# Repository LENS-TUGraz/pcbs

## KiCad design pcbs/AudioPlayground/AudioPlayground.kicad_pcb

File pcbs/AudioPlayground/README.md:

# LE Audio Playground

**An open hardware platform for Bluetooth LE Audio research, prototyping, and teaching.**

The **LE Audio Playground** is a compact development platform designed to make experimenting with **Bluetooth LE Audio** simple and accessible. Built around the **Nordic nRF5340**, it combines a powerful Bluetooth SoC with stereo audio, integrated debugging, USB connectivity, battery operation, and flexible expansion in a single open hardware platform.

Designed at **Graz University of Technology**, the board provides a practical foundation for LE Audio research, prototyping, and education while remaining fully open and easy to extend.

## Highlights

- **Nordic nRF5340** dual-core Bluetooth SoC
- **MAX9867 stereo audio codec**
- Analog audio input and output
- **USB Audio** connectivity
- Onboard digital **PDM microphones**
- Integrated **SEGGER J-Link** debugging and programming
- Single **USB-C** connection
- USB and **LiPo/Li-ion battery operation**
- Onboard antenna
- Expansion headers for custom hardware and audio interfaces
- Fully **open KiCad hardware design**

## Open Hardware

The complete schematic and PCB design are available in this repository and can be modified directly in **KiCad**.

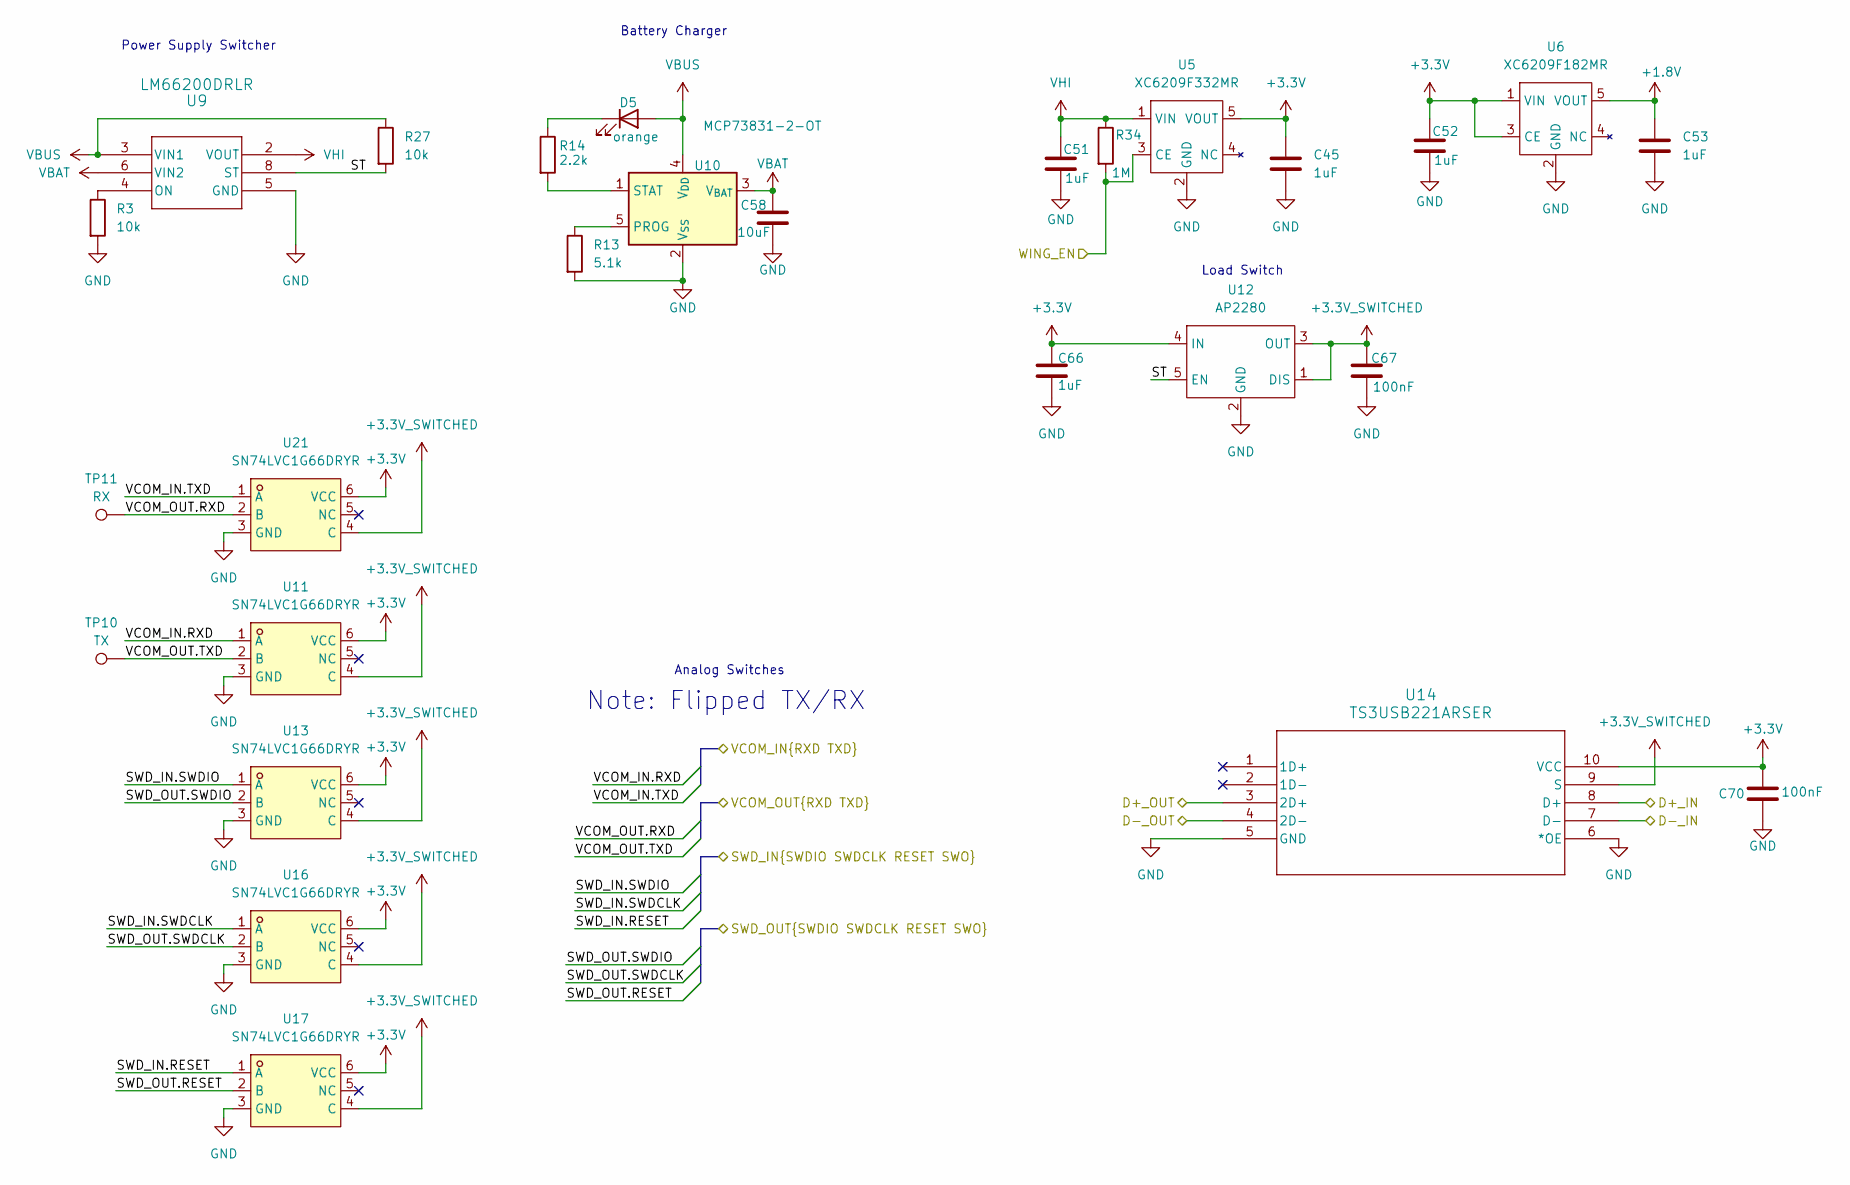
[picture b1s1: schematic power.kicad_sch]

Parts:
C45, C51, C52, C53, C66: 1uF; C_0402_1005Metric; MOUSER 81-GRM155Z71A105KE1D
C58: 10uF; C_0402_1005Metric; MOUSER 187-CL05A106MQ5NRNC
C67, C70: 100nF; C_0402_1005Metric; MOUSER 80-C0402C104M4R
D5: orange; LED_0402_1005Metric; MOUSER 78-VLMO1500-GS08
R3, R27: 10k; R_0402_1005Metric; MOUSER 660-RN73R1ETP1002F50
R13: 5.1k; R_0402_1005Metric; MOUSER 594-MCS04020C5102FE0
R14: 2.2k; R_0402_1005Metric; MOUSER 603-AC0402FR-7D2K2L
R34: 1M; R_0402_1005Metric; MOUSER 279-CRGCQ0402J1M0
TP10: TX; TestPoint_Pad_D1.0mm
TP11: RX; TestPoint_Pad_D1.0mm
U5: XC6209F332MR; SOT-23-5_HandSoldering; MOUSER 865-XC6209F332MR-G
U6: XC6209F182MR; SOT-23-5_HandSoldering; MOUSER 865-XC6209F332MR-G
U9: LM66200DRLR; LM662; MOUSER 595-LM66200DRLR
U10: MCP73831-2-OT; SOT-23-5; MOUSER 579-MCP73832T2DFI/OT
U11, U13, U16, U17, U21: SN74LVC1G66DRYR; LCSC Part C507245
U12: AP2280; SOT-23-5; MOUSER 621-AP2280-1WG-7
U14: TS3USB221ARSER; TS3USB221A; LCSC C128396

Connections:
+1.8V: C53.1, U6.5 (VOUT); also elsewhere on the board
+3.3V: C45.1, C52.1, C66.1, C70.1, U5.5 (VOUT), U6.1 (VIN), U6.3 (CE), U11.6 (VCC), U12.4 (IN), U13.6 (VCC), U14.10 (VCC), U16.6 (VCC), U17.6 (VCC), U21.6 (VCC); also elsewhere on the board
+3.3V_SWITCHED: C67.1, U11.4 (C), U12.1 (DIS), U12.3 (OUT), U13.4 (C), U14.9 (S), U16.4 (C), U17.4 (C), U21.4 (C); also elsewhere on the board
/IO/WING_EN: R34.2, U5.3 (CE); also elsewhere on the board
/Interface MCU/SWD.RESET: U17.1 (A); also elsewhere on the board
/Interface MCU/SWD.SWDCLK: U16.1 (A); also elsewhere on the board
/Interface MCU/SWD.SWDIO: U13.1 (A); also elsewhere on the board
/Interface MCU/VCOM.RXD: U11.1 (A); also elsewhere on the board
/Interface MCU/VCOM.TXD: U21.1 (A); also elsewhere on the board
/MCU/D+: U14.3 (2D+); also elsewhere on the board
/MCU/D-: U14.4 (2D-); also elsewhere on the board
/MCU/SWD.RESET: U17.2 (B); also elsewhere on the board
/MCU/SWD.SWDCLK: U16.2 (B); also elsewhere on the board
/MCU/SWD.SWDIO: U13.2 (B); also elsewhere on the board
/MCU/VCOM.RXD: TP11.1, U21.2 (B); also elsewhere on the board
/MCU/VCOM.TXD: TP10.1, U11.2 (B); also elsewhere on the board
/Power/D+_IN: U14.8 (D+); also elsewhere on the board
/Power/D-_IN: U14.7 (D-); also elsewhere on the board
/Power/ST: R27.2, U9.8 (ST), U12.5 (EN)
GND: C45.2, C51.2, C52.2, C53.2, C58.2, C66.2, C67.2, C70.2, R3.2, R13.2, U5.2 (GND), U6.2 (GND), U9.1 (GND), U9.5 (GND), U10.2 (V_{SS}), U11.3 (GND), U12.2 (GND), U13.3 (GND), U14.5 (GND), U14.6 (*OE), U16.3 (GND), U17.3 (GND), U21.3 (GND); also elsewhere on the board
unnamed: D5.1 (K), R14.1
unnamed: R3.1, U9.4 (ON)
unnamed: R13.1, U10.5 (PROG)
unnamed: R14.2, U10.1 (STAT)
VBAT: C58.1, U9.6 (VIN2), U10.3 (V_{BAT}); also elsewhere on the board
VBUS: D5.2 (A), R27.1, U9.3 (VIN1), U10.4 (V_{DD}); also elsewhere on the board
VHI: C51.1, R34.1, U5.1 (VIN), U9.2 (VOUT), U9.7 (VOUT); also elsewhere on the board

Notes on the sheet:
Note: Flipped TX/RX
Analog Switches
Battery Charger
Power Supply Switcher
Load Switch

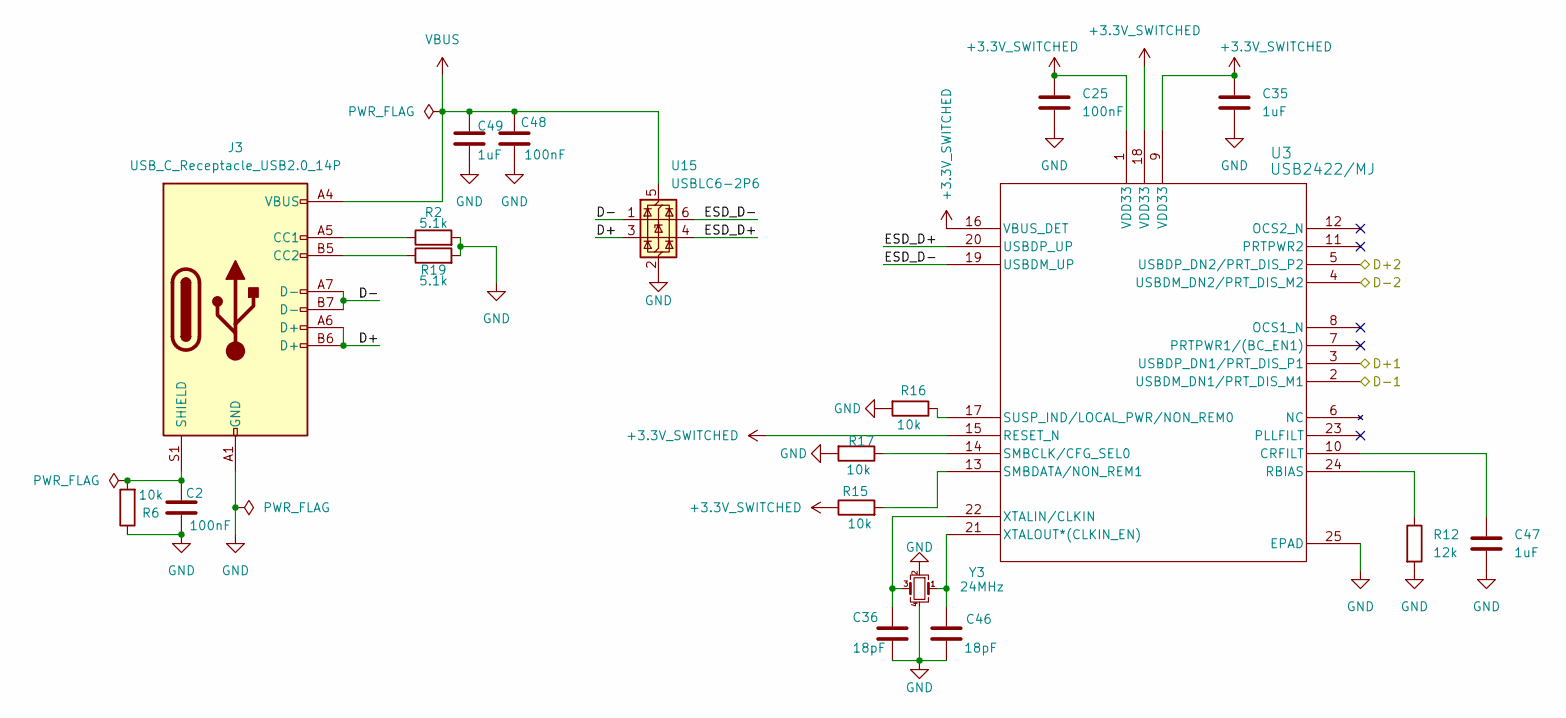
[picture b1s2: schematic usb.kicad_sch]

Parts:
C2, C25, C48: 100nF; C_0402_1005Metric; MOUSER 80-C0402C104M4R
C35, C47, C49: 1uF; C_0402_1005Metric; MOUSER 81-GRM155Z71A105KE1D
C36, C46: 18pF; C_0402_1005Metric; MOUSER 581-04025A180F4T2A
J3: USB_C_Receptacle_USB2.0_14P; USB_C_Receptacle_GCT_USB4105-xx-A_16P_TopMnt_Horizontal; MOUSER 640-USB4105-GF-A
R2, R19: 5.1k; R_0402_1005Metric; MOUSER 667-ERJ-2RHD5101X
R6: 10k; R_0402_1005Metric; MOUSER 660-RN73R1ETP1002F50
R12: 12k; R_0402_1005Metric; MOUSER 652-CR0402FX-1202GLF
R15, R16, R17: 10k; R_0402_1005Metric; MOUSER 594-MCS04020C5102FE0
U3: USB2422/MJ; USB2422; MOUSER 579-USB2422T/MJ
U15: USBLC6-2P6; SOT-666; LCSC C15999
Y3: 24MHz; Crystal_SMD_3225-4Pin_3.2x2.5mm; MOUSER 732-322524F20GAC0

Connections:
+3.3V_SWITCHED: C25.1, C35.1, R15.1, U3.1 (VDD33), U3.9 (VDD33), U3.15 (RESET_N), U3.16 (VBUS_DET), U3.18 (VDD33); also elsewhere on the board
/Interface MCU/D+: U3.5 (USBDP_DN2/PRT_DIS_P2); also elsewhere on the board
/Interface MCU/D-: U3.4 (USBDM_DN2/PRT_DIS_M2); also elsewhere on the board
/Power/D+_IN: U3.3 (USBDP_DN1/PRT_DIS_P1); also elsewhere on the board
/Power/D-_IN: U3.2 (USBDM_DN1/PRT_DIS_M1); also elsewhere on the board
/USB Port/D+: J3.A6 (D+), J3.B6 (D+), U15.3 (I/O2)
/USB Port/D-: J3.A7 (D-), J3.B7 (D-), U15.1 (I/O1)
/USB Port/ESD_D+: U3.20 (USBDP_UP), U15.4 (I/O2)
/USB Port/ESD_D-: U3.19 (USBDM_UP), U15.6 (I/O1)
GND: C2.2, C25.2, C35.2, C36.2, C46.2, C47.2, C48.2, C49.2, J3.A1 (GND), J3.A12 (GND), J3.B1 (GND), J3.B12 (GND), R2.2, R6.1, R12.2, R16.2, R17.2, R19.2, U3.25 (EPAD), U15.2 (GND), Y3.2, Y3.4; also elsewhere on the board
unnamed: J3.A5 (CC1), R2.1
unnamed: J3.B5 (CC2), R19.1
unnamed: C2.1, J3.S1 (SHIELD), R6.2
unnamed: C47.1, U3.10 (CRFILT)
unnamed: R12.1, U3.24 (RBIAS)
unnamed: R17.1, U3.14 (SMBCLK/CFG_SEL0)
unnamed: R15.2, U3.13 (SMBDATA/NON_REM1)
unnamed: R16.1, U3.17 (SUSP_IND/LOCAL_PWR/NON_REM0)
unnamed: C36.1, U3.22 (XTALIN/CLKIN), Y3.3
unnamed: C46.1, U3.21 (XTALOUT*(CLKIN_EN)), Y3.1
VBUS: C48.1, C49.1, J3.A4 (VBUS), J3.A9 (VBUS), J3.B4 (VBUS), J3.B9 (VBUS), U15.5 (VBUS); also elsewhere on the board

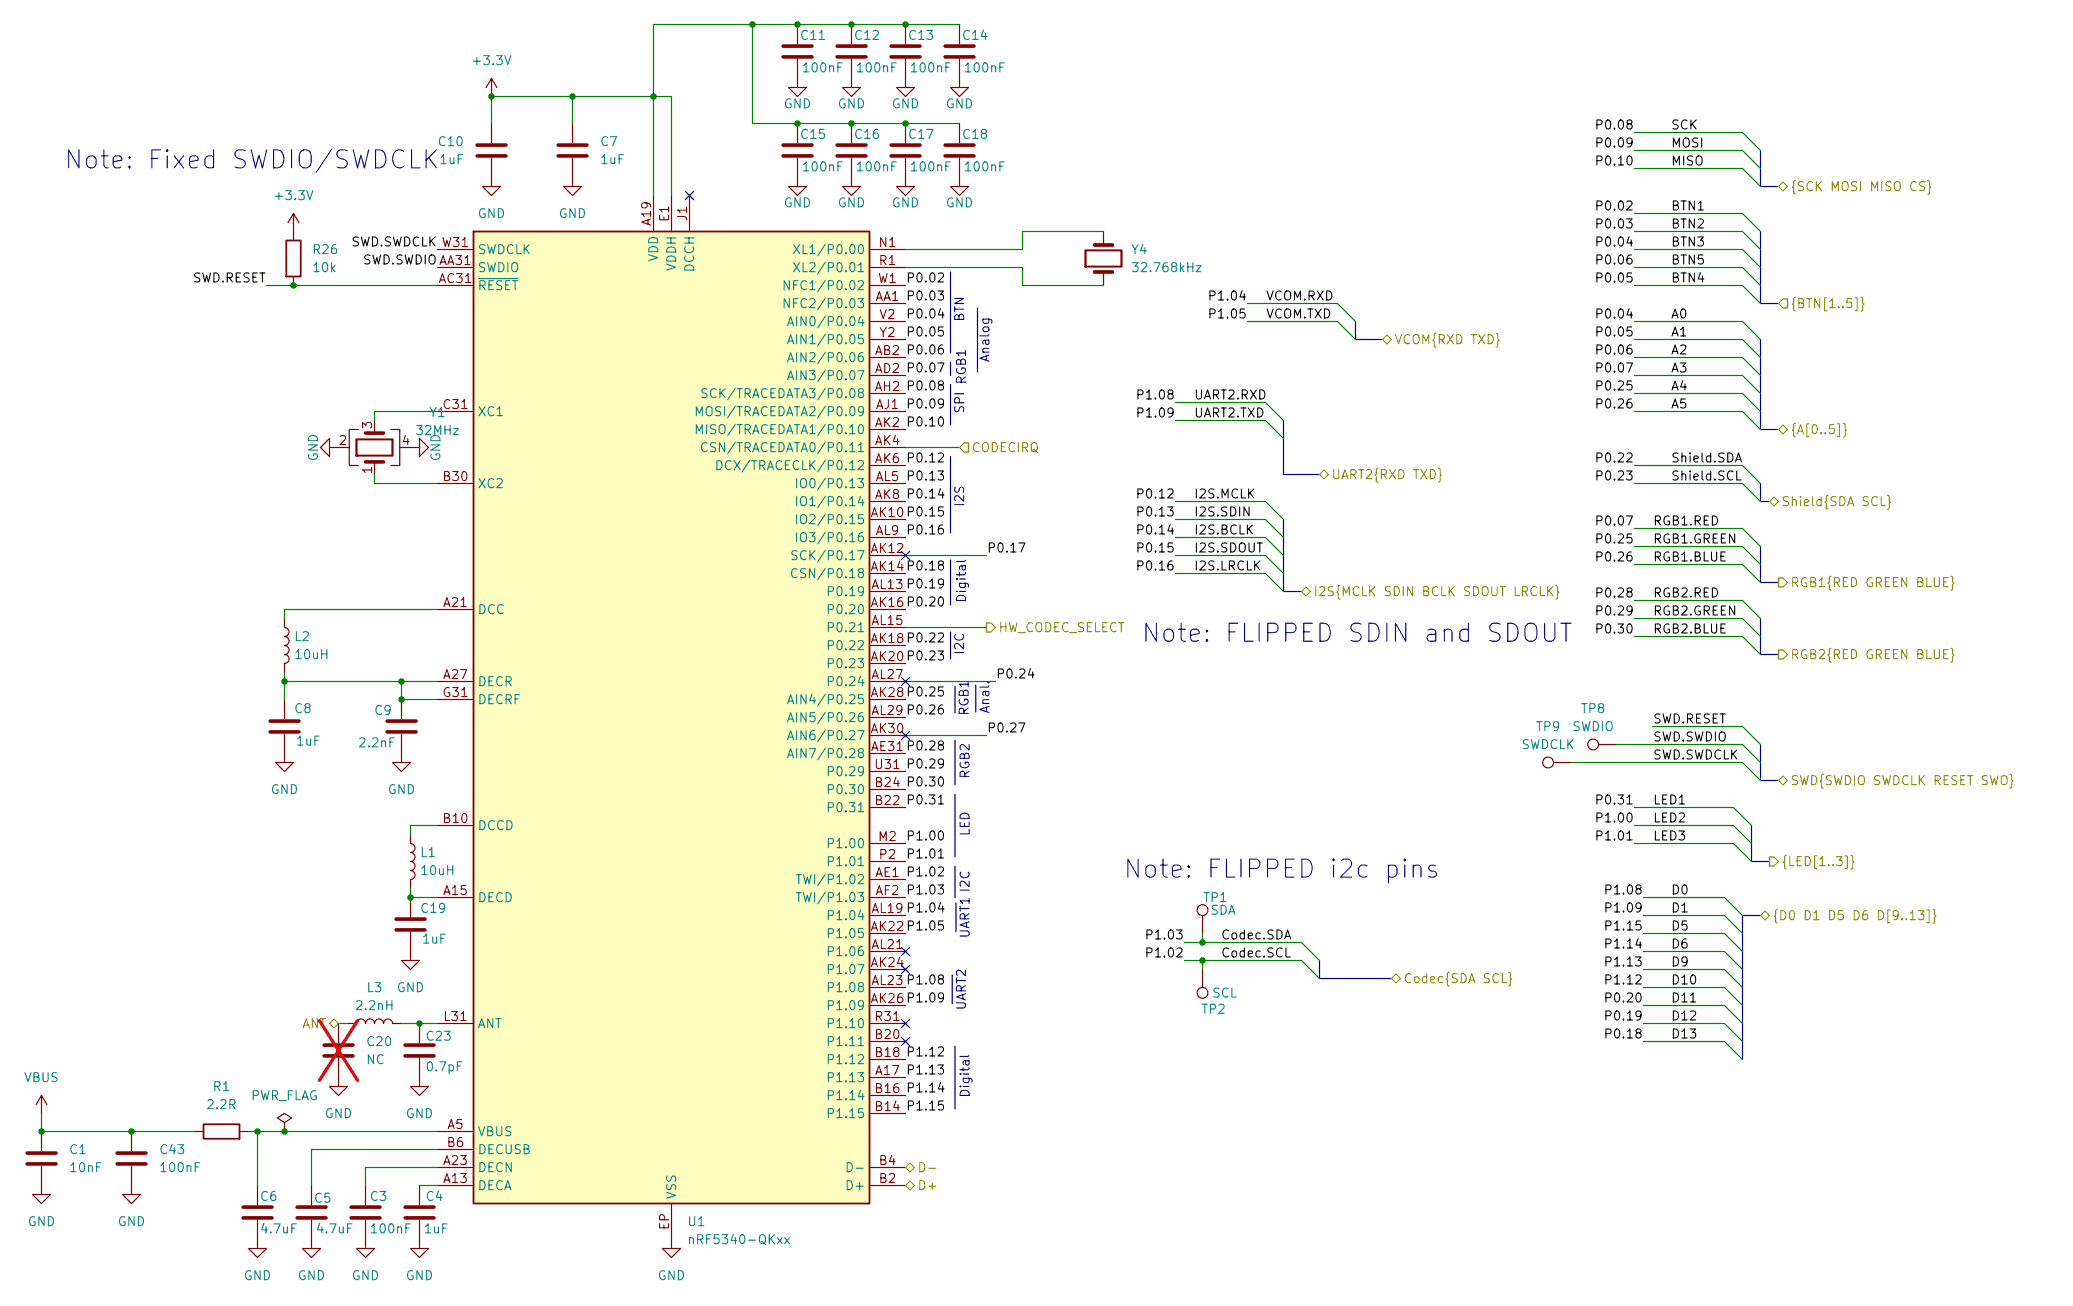
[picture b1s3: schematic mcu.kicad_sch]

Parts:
C1: 10nF; C_0402_1005Metric; MOUSER 80-C0402C103K8RLR
C3, C11, C12, C13, C14, C15, C16, C17, C18, C43: 100nF; C_0402_1005Metric; MOUSER 80-C0402C104M4R
C4, C7, C8, C10, C19: 1uF; C_0402_1005Metric; MOUSER 81-GRM155Z71A105KE1D
C5, C6: 4.7uF; C_0402_1005Metric; MOUSER 603-CC0402KR5R6BB475
C9: 2.2nF; C_0402_1005Metric; MOUSER 581-04023C222KAT2A
C20: NC; C_0402_1005Metric; not fitted
C23: 0.7pF; C_0402_1005Metric; MOUSER 581-04025U0R7BAT2A
L1, L2: 10uH; L_0402_1005Metric; MOUSER 81-LQW15DN100M00D
L3: 2.2nH; L_0402_1005Metric; MOUSER 815-AISCQ0402HQ2N2CT
R1: 2.2R; R_0402_1005Metric; MOUSER 667-ERJ-U02F2R20X
R26: 10k; R_0402_1005Metric; MOUSER 660-RN73R1ETP1002F50
TP1: SDA; TestPoint_Pad_D1.0mm
TP2: SCL; TestPoint_Pad_D1.0mm
TP8: SWDIO; TestPoint_Pad_D1.0mm
TP9: SWDCLK; TestPoint_Pad_D1.0mm
U1: nRF5340-QKxx; Nordic_AQFN-94-1EP_7x7mm_P0.4mm; MOUSER 949-NRF5340-QKAA-R7
Y1: 32MHz; Crystal_SMD_3225-4Pin_3.2x2.5mm; MOUSER 581-CX3225GB32DHEQCC
Y4: 32.768kHz; Crystal_SMD_3215-2Pin_3.2x1.5mm; MOUSER 732-FC135-32.76KAAC3

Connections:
+3.3V: C7.1, C10.2, C11.1, C12.1, C13.1, C14.1, C15.1, C16.1, C17.1, C18.1, R26.1, U1.A19 (VDD), U1.AC1 (VDD), U1.AG1 (VDD), U1.AJ31 (VDD), U1.AL3 (VDD), U1.AL7 (VDD), U1.AL11 (VDD), U1.AL17 (VDD), U1.AL25 (VDD), U1.B8 (VDD), U1.B28 (VDD), U1.C1 (VDD), U1.E1 (VDDH), U1.E31 (VDD), U1.L1 (VDD), U1.N31 (VDD), U1.U1 (VDD); also elsewhere on the board
/Audio Codec/Codec.SCL: TP2.1, U1.AE1 (TWI/P1.02); also elsewhere on the board
/Audio Codec/Codec.SDA: TP1.1, U1.AF2 (TWI/P1.03); also elsewhere on the board
/Audio Codec/I2S.BCLK: U1.AK8 (IO1/P0.14); also elsewhere on the board
/Audio Codec/I2S.LRCLK: U1.AL9 (IO3/P0.16); also elsewhere on the board
/Audio Codec/I2S.MCLK: U1.AK6 (DCX/TRACECLK/P0.12); also elsewhere on the board
/Audio Codec/I2S.SDIN: U1.AL5 (IO0/P0.13); also elsewhere on the board
/Audio Codec/I2S.SDOUT: U1.AK10 (IO2/P0.15); also elsewhere on the board
/Audio Codec/IRQ: U1.AK4 (CSN/TRACEDATA0/P0.11); also elsewhere on the board
/IO/A0: U1.V2 (AIN0/P0.04); also elsewhere on the board
/IO/A1: U1.Y2 (AIN1/P0.05); also elsewhere on the board
/IO/A2: U1.AB2 (AIN2/P0.06); also elsewhere on the board
/IO/A3: U1.AD2 (AIN3/P0.07); also elsewhere on the board
/IO/A4: U1.AK28 (AIN4/P0.25); also elsewhere on the board
/IO/A5: U1.AL29 (AIN5/P0.26); also elsewhere on the board
/IO/ANT: C20.1, L3.1; also elsewhere on the board
/IO/BTN1: U1.W1 (NFC1/P0.02); also elsewhere on the board
/IO/BTN2: U1.AA1 (NFC2/P0.03); also elsewhere on the board
/IO/D0: U1.AL23 (P1.08); also elsewhere on the board
/IO/D1: U1.AK26 (P1.09); also elsewhere on the board
/IO/D5: U1.B14 (P1.15); also elsewhere on the board
/IO/D6: U1.B16 (P1.14); also elsewhere on the board
/IO/D9: U1.A17 (P1.13); also elsewhere on the board
/IO/D10: U1.B18 (P1.12); also elsewhere on the board
/IO/D11: U1.AK16 (P0.20); also elsewhere on the board
/IO/D12: U1.AL13 (P0.19); also elsewhere on the board
/IO/D13: U1.AK14 (CSN/P0.18); also elsewhere on the board
/IO/LED1: U1.B22 (P0.31); also elsewhere on the board
/IO/LED2: U1.M2 (P1.00); also elsewhere on the board
/IO/LED3: U1.P2 (P1.01); also elsewhere on the board
/IO/MISO: U1.AK2 (MISO/TRACEDATA1/P0.10); also elsewhere on the board
/IO/MOSI: U1.AJ1 (MOSI/TRACEDATA2/P0.09); also elsewhere on the board
/IO/SCK: U1.AH2 (SCK/TRACEDATA3/P0.08); also elsewhere on the board
/IO/SCL: U1.AK20 (P0.23); also elsewhere on the board
/IO/SDA: U1.AK18 (P0.22); also elsewhere on the board
/MCU/D+: U1.B2 (D+); also elsewhere on the board
/MCU/D-: U1.B4 (D-); also elsewhere on the board
/MCU/HW_CODEC_SELECT: U1.AL15 (P0.21)
/MCU/P0.17: U1.AK12 (SCK/P0.17)
/MCU/P0.24: U1.AL27 (P0.24)
/MCU/P0.27: U1.AK30 (AIN6/P0.27)
/MCU/RGB2.BLUE: U1.B24 (P0.30)
/MCU/RGB2.GREEN: U1.U31 (P0.29)
/MCU/RGB2.RED: U1.AE31 (AIN7/P0.28)
/MCU/SWD.RESET: R26.2, U1.AC31 (~RESET); also elsewhere on the board
/MCU/SWD.SWDCLK: TP9.1, U1.W31 (SWDCLK); also elsewhere on the board
/MCU/SWD.SWDIO: TP8.1, U1.AA31 (SWDIO); also elsewhere on the board
/MCU/VCOM.RXD: U1.AL19 (P1.04); also elsewhere on the board
/MCU/VCOM.TXD: U1.AK22 (P1.05); also elsewhere on the board
GND: C1.2, C3.2, C4.2, C5.2, C6.2, C7.2, C8.2, C9.2, C10.1, C11.2, C12.2, C13.2, C14.2, C15.2, C16.2, C17.2, C18.2, C19.2, C20.2, C23.2, C43.2, U1.EP (VSS), Y1.2, Y1.4; also elsewhere on the board
unnamed: C23.1, L3.2, U1.L31 (ANT)
unnamed: L2.1, U1.A21 (DCC)
unnamed: L1.1, U1.B10 (DCCD)
unnamed: C4.1, U1.A13 (DECA)
unnamed: C19.1, L1.2, U1.A15 (DECD)
unnamed: C3.1, U1.A23 (DECN)
unnamed: C8.1, C9.1, L2.2, U1.A27 (DECR), U1.G31 (DECRF)
unnamed: C5.1, U1.B6 (DECUSB)
unnamed: C6.1, R1.2, U1.A5 (VBUS)
unnamed: U1.C31 (XC1), Y1.3
unnamed: U1.B30 (XC2), Y1.1
unnamed: U1.N1 (XL1/P0.00), Y4.2
unnamed: U1.R1 (XL2/P0.01), Y4.1
VBUS: C1.1, C43.1, R1.1; also elsewhere on the board

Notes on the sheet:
RGB2
I2C
Analog
BTN
SPI
LED
Anal.
RGB1
Digital
UART2
I2S
Note: Fixed SWDIO/SWDCLK
Note: FLIPPED i2c pins
Note: FLIPPED SDIN and SDOUT
UART1

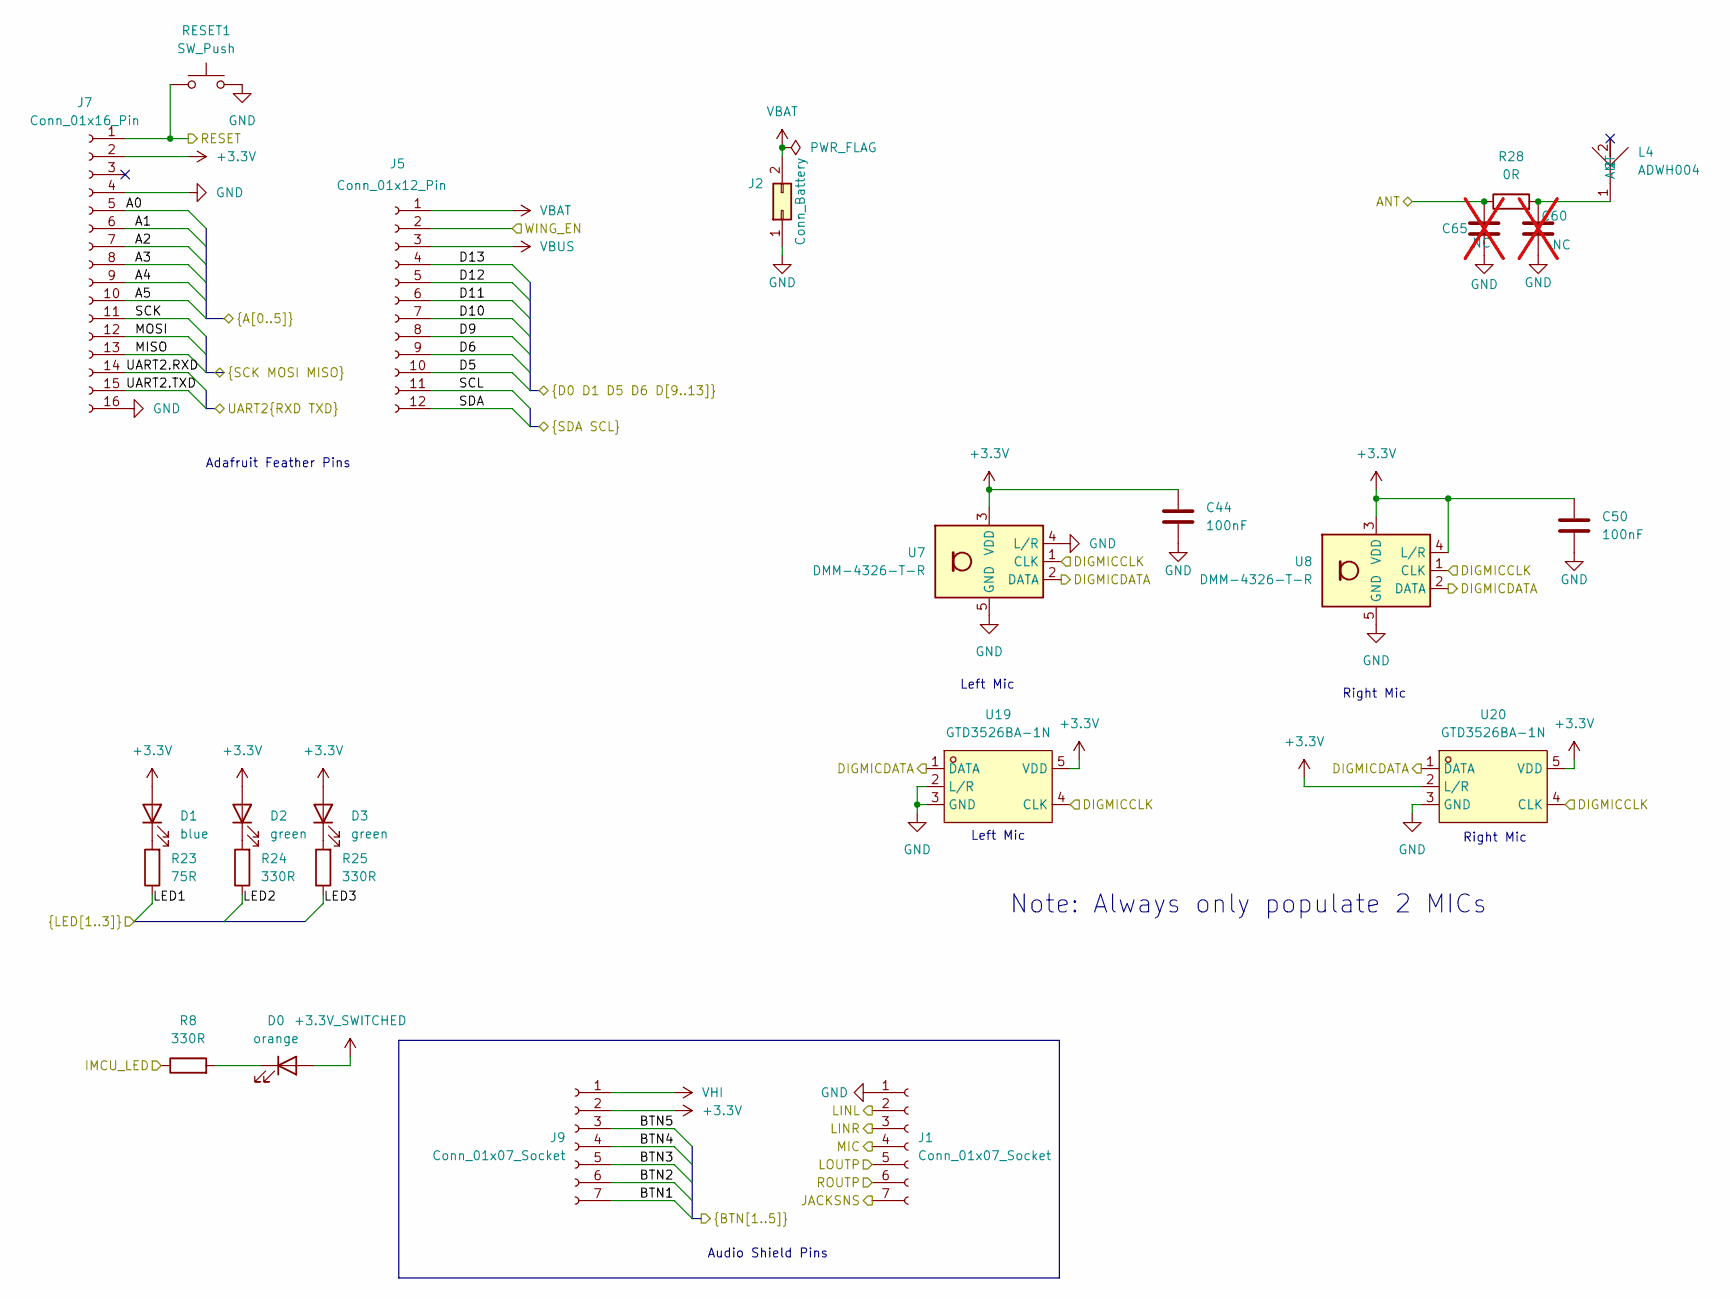
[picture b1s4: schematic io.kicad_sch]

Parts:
C44, C50: 100nF; C_0402_1005Metric; MOUSER 80-C0402C104M4R
C60, C65: NC; C_0402_1005Metric; not fitted
D0: orange; LED_0402_1005Metric; MOUSER 78-VLMO1500-GS08
D1: blue; LED_0402_1005Metric; MOUSER 78-VLMB1500-GS08
D2, D3: green; LED_0402_1005Metric; MOUSER 720-LTQH9GQ2S225
J1, J9: Conn_01x07_Socket; PinSocket_1x07_P2.54mm_Vertical; MOUSER 571-215297-5
J2: Conn_Battery; JST_S2B-PH-SM4-TB; MOUSER 474-PRT-09749
J5: Conn_01x12_Pin; PinSocket_1x12_P2.54mm_Vertical; MOUSER 710-61301211821
J7: Conn_01x16_Pin; PinSocket_1x16_P2.54mm_Vertical; MOUSER 200-CES11601TS
L4: ADWH004; LCSC C42414493
R8, R24, R25: 330R; R_0402_1005Metric; MOUSER 603-RC0402JR-7D330RL
R23: 75R; R_0402_1005Metric; MOUSER 603-RC0402JR-7D330RL
R28: 0R; R_0402_1005Metric; LCSC C17168
RESET1: SW_Push; SW_SPST_B3U-1000P; MOUSER 653-B3U-1000P
U7, U8: DMM-4326-T-R; MOUSER 665-DMM-4326-T-R
U19, U20: GTD3526BA-1N; LCSC Part C50275765

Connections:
+3.3V: C44.2, C50.2, D1.2 (A), D2.2 (A), D3.2 (A), J7.2, J9.2, U7.3 (VDD), U8.3 (VDD), U8.4 (L/R), U19.5 (VDD), U20.2 (L/R), U20.5 (VDD); also elsewhere on the board
+3.3V_SWITCHED: D0.2 (A); also elsewhere on the board
/Audio Codec/DIGMICCLK: U7.1 (CLK), U8.1 (CLK), U19.4 (CLK), U20.4 (CLK); also elsewhere on the board
/Audio Codec/DIGMICDATA: U7.2 (DATA), U8.2 (DATA), U19.1 (DATA), U20.1 (DATA); also elsewhere on the board
/Audio Codec/JACKSNS: J1.7; also elsewhere on the board
/Audio Codec/LINL: J1.2; also elsewhere on the board
/Audio Codec/LINR: J1.3; also elsewhere on the board
/Audio Codec/LOUTP: J1.5; also elsewhere on the board
/Audio Codec/MIC: J1.4; also elsewhere on the board
/Audio Codec/ROUTP: J1.6; also elsewhere on the board
/IO/A0: J7.5, J9.5; also elsewhere on the board
/IO/A1: J7.6, J9.4; also elsewhere on the board
/IO/A2: J7.7, J9.3; also elsewhere on the board
/IO/A3: J7.8; also elsewhere on the board
/IO/A4: J7.9; also elsewhere on the board
/IO/A5: J7.10; also elsewhere on the board
/IO/ANT: C65.2, R28.1; also elsewhere on the board
/IO/BTN1: J9.7; also elsewhere on the board
/IO/BTN2: J9.6; also elsewhere on the board
/IO/D0: J7.14; also elsewhere on the board
/IO/D1: J7.15; also elsewhere on the board
/IO/D5: J5.10; also elsewhere on the board
/IO/D6: J5.9; also elsewhere on the board
/IO/D9: J5.8; also elsewhere on the board
/IO/D10: J5.7; also elsewhere on the board
/IO/D11: J5.6; also elsewhere on the board
/IO/D12: J5.5; also elsewhere on the board
/IO/D13: J5.4; also elsewhere on the board
/IO/IMCU_LED: R8.1; also elsewhere on the board
/IO/LED1: R23.1; also elsewhere on the board
/IO/LED2: R24.1; also elsewhere on the board
/IO/LED3: R25.1; also elsewhere on the board
/IO/MISO: J7.13; also elsewhere on the board
/IO/MOSI: J7.12; also elsewhere on the board
/IO/SCK: J7.11; also elsewhere on the board
/IO/SCL: J5.11; also elsewhere on the board
/IO/SDA: J5.12; also elsewhere on the board
/IO/WING_EN: J5.2; also elsewhere on the board
/MCU/SWD.RESET: J7.1, RESET1.1; also elsewhere on the board
GND: C44.1, C50.1, C60.1, C65.1, J1.1, J2.1, J7.4, J7.16, RESET1.2, U7.4 (L/R), U7.5 (GND), U8.5 (GND), U19.2 (L/R), U19.3 (GND), U20.3 (GND); also elsewhere on the board
unnamed: D0.1 (K), R8.2
unnamed: D1.1 (K), R23.2
unnamed: D2.1 (K), R24.2
unnamed: D3.1 (K), R25.2
unnamed: C60.2, L4.1 (ANT), R28.2
VBAT: J2.2, J5.1; also elsewhere on the board
VBUS: J5.3; also elsewhere on the board
VHI: J9.1; also elsewhere on the board

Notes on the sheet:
Left Mic
Note: Always only populate 2 MICs
Right Mic
Adafruit Feather Pins
Audio Shield Pins

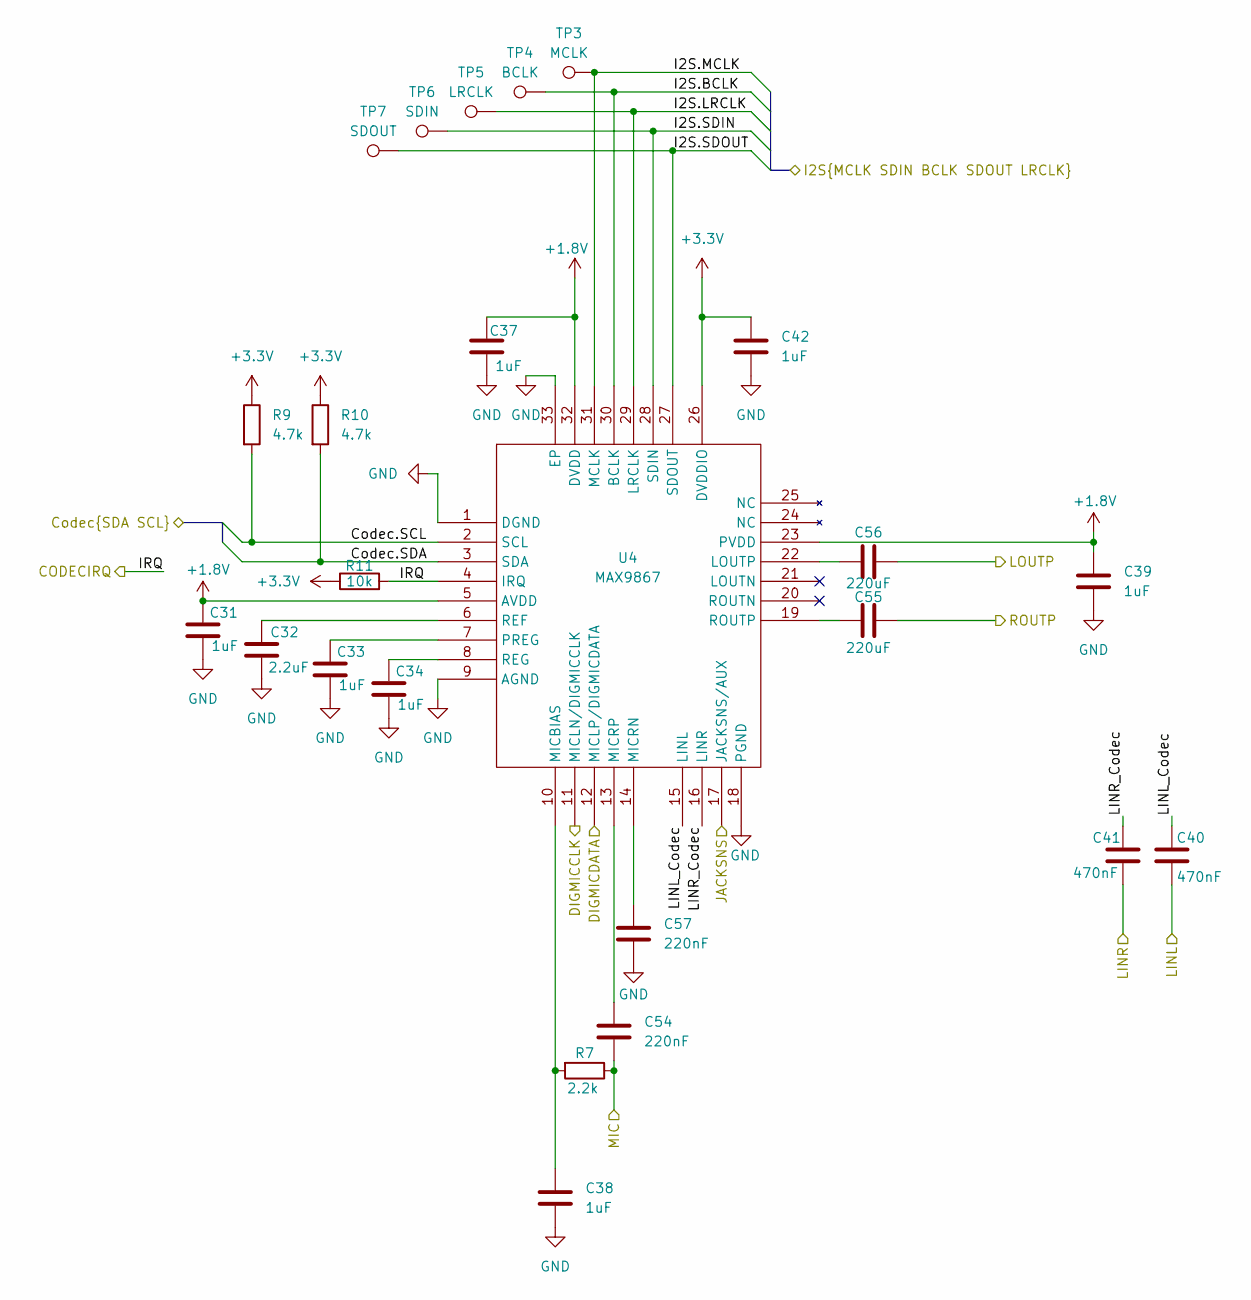
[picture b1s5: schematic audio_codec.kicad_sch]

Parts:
C31, C33, C34, C37, C38, C39, C42: 1uF; C_0402_1005Metric; MOUSER 81-GRM155Z71A105KE1D
C32: 2.2uF; C_0402_1005Metric; MOUSER 81-GRM155Z71A225KE4D
C40, C41: 470nF; C_0402_1005Metric; MOUSER 963-BASJ105SB7474KF
C54, C57: 220nF; C_0402_1005Metric; MOUSER 963-JMK105B7224KV-F
C55, C56: 220uF; C_1206_3216Metric; MOUSER 81-GRM31CR60E227ME1K
R7: 2.2k; R_0402_1005Metric; MOUSER 603-AC0402FR-7D2K2L
R9, R10: 4.7k; R_0402_1005Metric; MOUSER 603-RC0402FR-7D4K7L
R11: 10k; R_0402_1005Metric; MOUSER 660-RN73R1ETP1002F50
TP3: MCLK; TestPoint_Pad_D1.0mm
TP4: BCLK; TestPoint_Pad_D1.0mm
TP5: LRCLK; TestPoint_Pad_D1.0mm
TP6: SDIN; TestPoint_Pad_D1.0mm
TP7: SDOUT; TestPoint_Pad_D1.0mm
U4: MAX9867; MOUSER 700-MAX9867ETJT

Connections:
+1.8V: C31.1, C37.2, C39.1, U4.5 (AVDD), U4.23 (PVDD), U4.32 (DVDD); also elsewhere on the board
+3.3V: C42.1, R9.1, R10.1, R11.1, U4.26 (DVDDIO); also elsewhere on the board
/Audio Codec/Codec.SCL: R9.2, U4.2 (SCL); also elsewhere on the board
/Audio Codec/Codec.SDA: R10.2, U4.3 (SDA); also elsewhere on the board
/Audio Codec/DIGMICCLK: U4.11 (MICLN/DIGMICCLK); also elsewhere on the board
/Audio Codec/DIGMICDATA: U4.12 (MICLP/DIGMICDATA); also elsewhere on the board
/Audio Codec/I2S.BCLK: TP4.1, U4.30 (BCLK); also elsewhere on the board
/Audio Codec/I2S.LRCLK: TP5.1, U4.29 (LRCLK); also elsewhere on the board
/Audio Codec/I2S.MCLK: TP3.1, U4.31 (MCLK); also elsewhere on the board
/Audio Codec/I2S.SDIN: TP6.1, U4.28 (SDIN); also elsewhere on the board
/Audio Codec/I2S.SDOUT: TP7.1, U4.27 (SDOUT); also elsewhere on the board
/Audio Codec/IRQ: R11.2, U4.4 (IRQ); also elsewhere on the board
/Audio Codec/JACKSNS: U4.17 (JACKSNS/AUX); also elsewhere on the board
/Audio Codec/LINL: C40.2; also elsewhere on the board
/Audio Codec/LINL_Codec: C40.1, U4.15 (LINL)
/Audio Codec/LINR: C41.2; also elsewhere on the board
/Audio Codec/LINR_Codec: C41.1, U4.16 (LINR)
/Audio Codec/LOUTP: C56.2; also elsewhere on the board
/Audio Codec/MIC: C54.2, R7.1; also elsewhere on the board
/Audio Codec/ROUTP: C55.2; also elsewhere on the board
GND: C31.2, C32.2, C33.2, C34.2, C37.1, C38.2, C39.2, C42.2, C57.2, U4.1 (DGND), U4.9 (AGND), U4.18 (PGND), U4.33 (EP); also elsewhere on the board
unnamed: C56.1, U4.22 (LOUTP)
unnamed: C38.1, R7.2, U4.10 (MICBIAS)
unnamed: C57.1, U4.14 (MICRN)
unnamed: C54.1, U4.13 (MICRP)
unnamed: C33.1, U4.7 (PREG)
unnamed: C32.1, U4.6 (REF)
unnamed: C34.1, U4.8 (REG)
unnamed: C55.1, U4.19 (ROUTP)

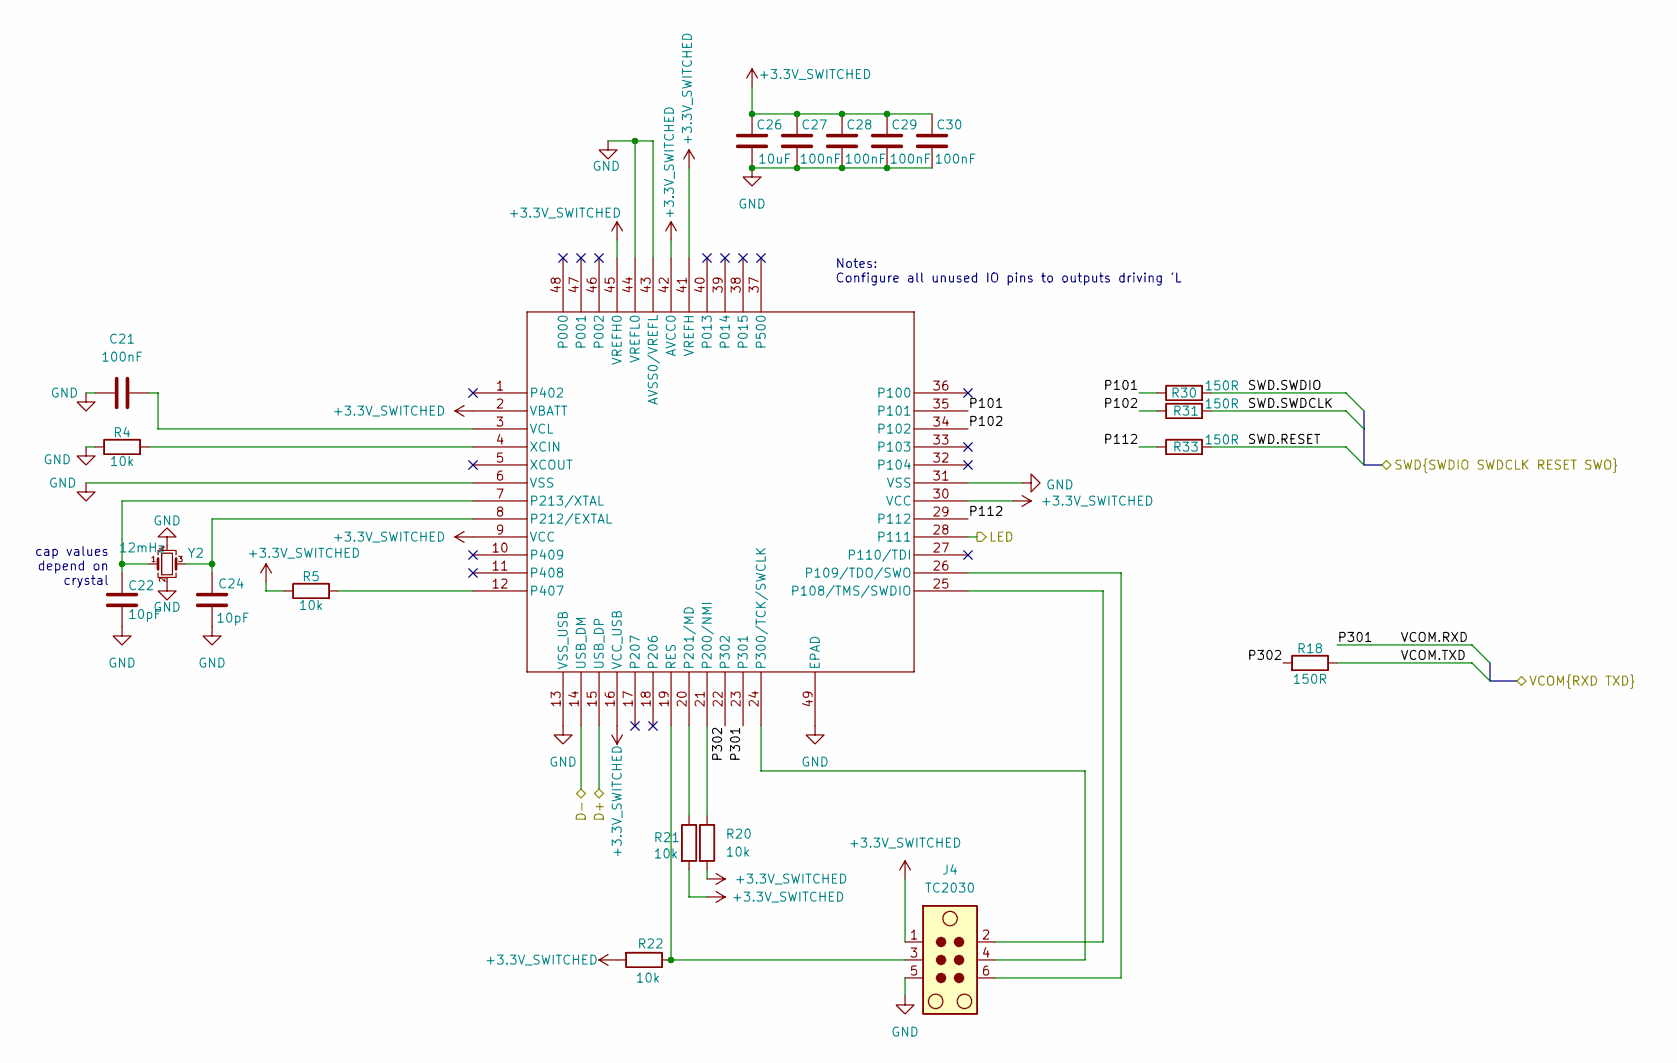
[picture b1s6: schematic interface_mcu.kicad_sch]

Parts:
C21, C27, C28, C29, C30: 100nF; C_0402_1005Metric; MOUSER 80-C0402C104M4R
C22, C24: 10pF; C_0402_1005Metric; MOUSER 581-04025A100DAT2A
C26: 10uF; C_0402_1005Metric; MOUSER 187-CL05A106MQ5NRNC
J4: TC2030; Tag-Connect_TC2030-IDC-NL_2x03_P1.27mm_Vertical
R4, R5, R20, R21, R22: 10k; R_0402_1005Metric; MOUSER 660-RN73R1ETP1002F50
R18, R30, R31, R33: 150R; R_0402_1005Metric; MOUSER 603-RC0402FR-7D150RL
U2: R7FA4M2AB3CNE; PWQN0048KC-A_REN; MOUSER 968-7FA4M2AB3CNE#AA0
Y2: 12mHz; Crystal_SMD_3225-4Pin_3.2x2.5mm; MOUSER 581-CX3225SB12DFPNCC

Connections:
+3.3V_SWITCHED: C26.1, C27.1, C28.1, C29.1, C30.1, J4.1, R5.1, R20.2, R21.2, R22.2, U2.2 (VBATT), U2.9 (VCC), U2.16 (VCC_USB), U2.30 (VCC), U2.41 (VREFH), U2.42 (AVCC0), U2.45 (VREFH0); also elsewhere on the board
/IO/IMCU_LED: U2.28 (P111); also elsewhere on the board
/Interface MCU/D+: U2.15 (USB_DP); also elsewhere on the board
/Interface MCU/D-: U2.14 (USB_DM); also elsewhere on the board
/Interface MCU/P101: R30.1, U2.35 (P101)
/Interface MCU/P102: R31.1, U2.34 (P102)
/Interface MCU/P112: R33.1, U2.29 (P112)
/Interface MCU/P302: R18.2, U2.22 (P302)
/Interface MCU/SWD.RESET: R33.2; also elsewhere on the board
/Interface MCU/SWD.SWDCLK: R31.2; also elsewhere on the board
/Interface MCU/SWD.SWDIO: R30.2; also elsewhere on the board
/Interface MCU/VCOM.RXD: U2.23 (P301); also elsewhere on the board
/Interface MCU/VCOM.TXD: R18.1; also elsewhere on the board
GND: C21.1, C22.2, C24.2, C26.2, C27.2, C28.2, C29.2, C30.2, J4.5, R4.1, U2.6 (VSS), U2.13 (VSS_USB), U2.31 (VSS), U2.43 (AVSS0/VREFL), U2.44 (VREFL0), U2.49 (EPAD), Y2.2, Y2.4; also elsewhere on the board
unnamed: J4.2, U2.25 (P108/TMS/SWDIO)
unnamed: J4.6, U2.26 (P109/TDO/SWO)
unnamed: R20.1, U2.21 (P200/NMI)
unnamed: R21.1, U2.20 (P201/MD)
unnamed: C24.1, U2.8 (P212/EXTAL), Y2.3
unnamed: C22.1, U2.7 (P213/XTAL), Y2.1
unnamed: J4.4, U2.24 (P300/TCK/SWCLK)
unnamed: R5.2, U2.12 (P407)
unnamed: J4.3, R22.1, U2.19 (RES)
unnamed: C21.2, U2.3 (VCL)
unnamed: R4.2, U2.4 (XCIN)

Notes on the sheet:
cap values depend on crystal
Notes: Configure all unused IO pins to outputs driving 'L
